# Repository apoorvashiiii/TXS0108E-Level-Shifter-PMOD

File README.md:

TXS0108E Bidirectional Level-Shifter PMOD

A compact, open-source 8-channel bidirectional voltage level-translation board adopting the standard PMOD form factor. Built around the Texas Instruments TXS0108E, this board facilitates seamless logic level conversion without requiring a dedicated direction control pin.

Designed natively in KiCad, this module is specifically optimized to bridge custom RISC-V cores and open silicon test environments with standard 3.3V or 5V sensors and peripherals.

🚀 Features

Auto-Direction Sensing:No DIR pin required; automatically detects the direction of data flow.
Wide Voltage Range:
Port A (Low Voltage): 1.2V to 3.6V
Port B (High Voltage): 1.65V to 5.5V 

High-Speed Protocol Support: Compatible with push-pull (SPI, UART) and open-drain (I2C) communication protocols.

Standard PMOD Interface: 12-pin (2x6) standard PMOD header layout for plug-and-play compatibility with FPGA development boards and microcontroller testbeds.

Signal Integrity: Carefully routed traces with localized 100nF decoupling capacitors on both VCCA and VCCB rails to ensure stable switching at high frequencies.

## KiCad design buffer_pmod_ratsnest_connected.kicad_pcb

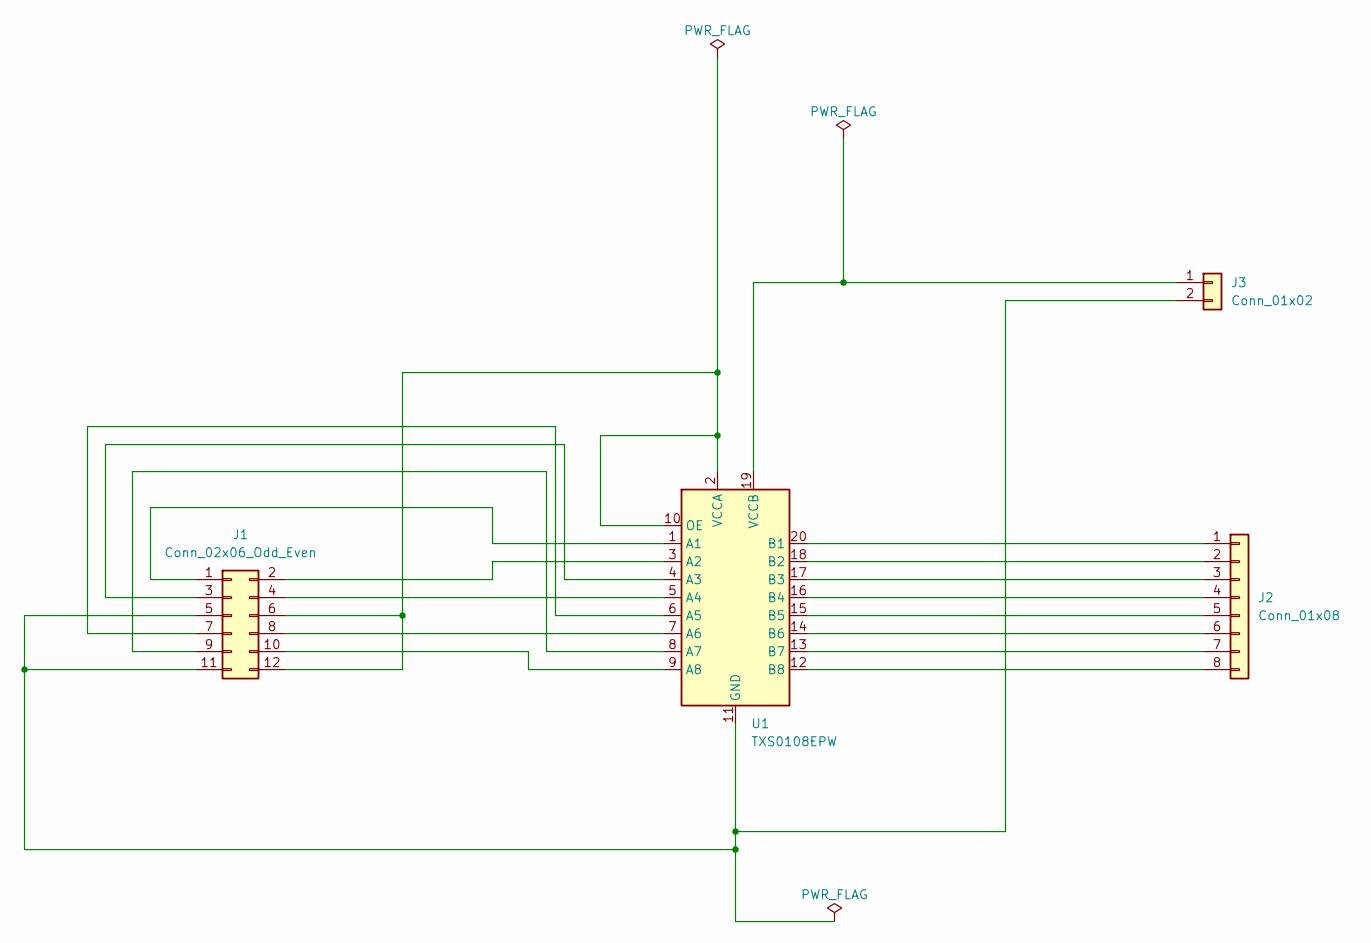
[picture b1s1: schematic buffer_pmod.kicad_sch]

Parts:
J1: Conn_02x06_Odd_Even; PinHeader_2x06_P2.54mm_Horizontal
J2: Conn_01x08; PinHeader_1x08_P2.54mm_Vertical
J3: Conn_01x02; PinHeader_1x02_P2.54mm_Vertical
U1: TXS0108EPW; TSSOP-20_4.4x6.5mm_P0.65mm

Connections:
unnamed: J1.1, U1.1 (A1)
unnamed: J1.2, U1.3 (A2)
unnamed: J1.3, U1.4 (A3)
unnamed: J1.4, U1.5 (A4)
unnamed: J1.7, U1.6 (A5)
unnamed: J1.8, U1.7 (A6)
unnamed: J1.9, U1.8 (A7)
unnamed: J1.10, U1.9 (A8)
unnamed: J1.5, J1.11, J3.2, U1.11 (GND)
unnamed: J1.6, J1.12, U1.2 (VCCA), U1.10 (OE)
unnamed: J2.1, U1.20 (B1)
unnamed: J2.2, U1.18 (B2)
unnamed: J2.3, U1.17 (B3)
unnamed: J2.4, U1.16 (B4)
unnamed: J2.5, U1.15 (B5)
unnamed: J2.6, U1.14 (B6)
unnamed: J2.7, U1.13 (B7)
unnamed: J2.8, U1.12 (B8)
unnamed: J3.1, U1.19 (VCCB)

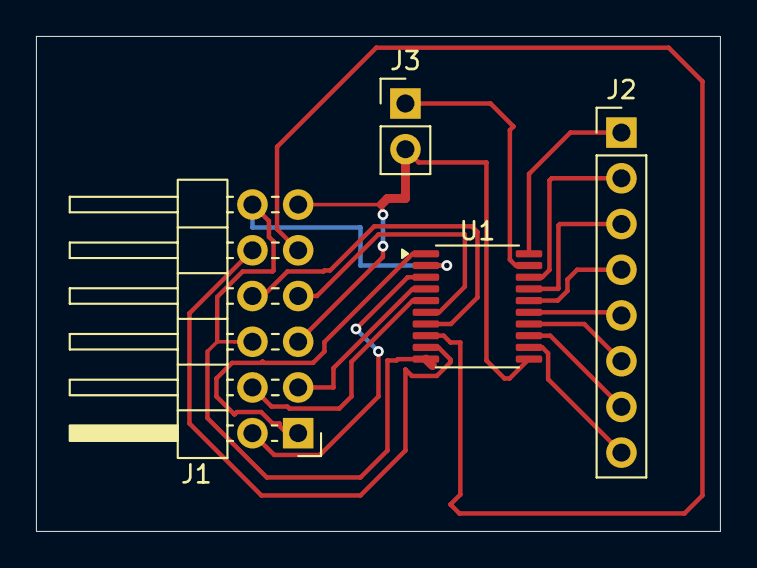
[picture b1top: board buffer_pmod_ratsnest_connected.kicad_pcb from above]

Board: 2 copper layers, 38.0 x 27.5 mm, 4 parts (0 on the bottom side), 19 nets.
